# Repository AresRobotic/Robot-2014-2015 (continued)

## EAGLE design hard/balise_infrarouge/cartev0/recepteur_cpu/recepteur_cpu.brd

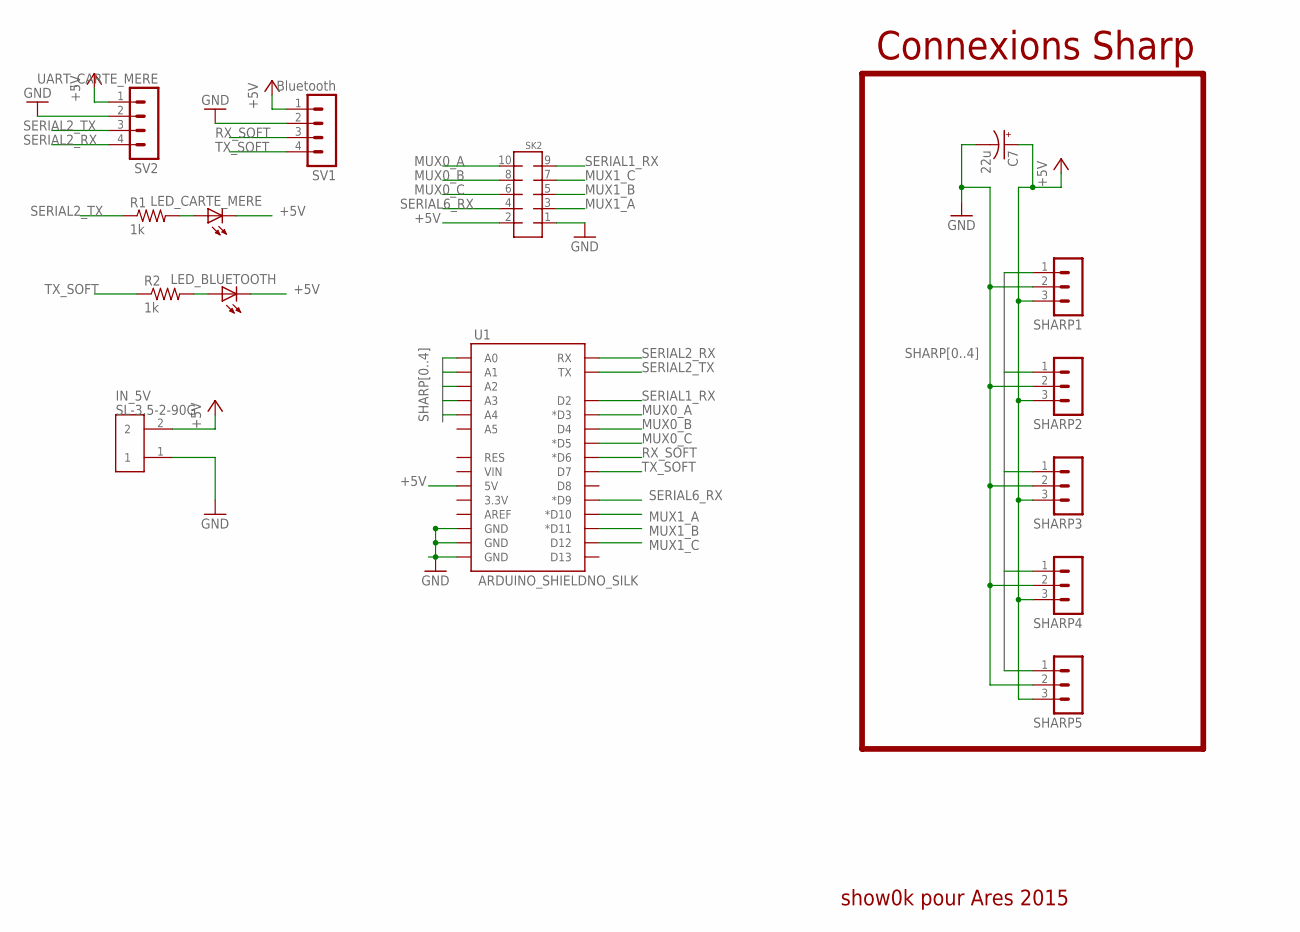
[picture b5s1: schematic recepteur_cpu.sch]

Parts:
C7: 22u; CPOL-RADIAL-100UF-25V
IN_5V: SL-3.5-2-90G
LED_BLUETOOTH: LEDCHIPLED_0805; CHIPLED_0805
LED_CARTE_MERE: LEDCHIPLED_0805; CHIPLED_0805
R1, R2: 1k; 0805
SHARP1, SHARP2, SHARP3, SHARP4, SHARP5: MA03-1
SK2: MMATCH-10-PTH; AMP-215079-10
SV1: Bluetooth; MA04-1
SV2: UART_CARTE_MERE; MA04-1
U1: ARDUINO_SHIELDNO_SILK; DUEMILANOVE_VIAS

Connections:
+5V: C7.1 (+), IN_5V.2, LED_BLUETOOTH.C, LED_CARTE_MERE.C, SHARP1.3, SHARP2.3, SHARP3.3, SHARP4.3, SHARP5.3, SK2.2, SV1.1, SV2.1, U1.5V
GND: C7.2 (-), IN_5V.1, SHARP1.2, SHARP2.2, SHARP3.2, SHARP4.2, SHARP5.2, SK2.1, SV1.2, SV2.2, U1.GND@0 (GND), U1.GND@1 (GND), U1.GND@2 (GND)
MUX0_A: SK2.10, U1.D3 (*D3)
MUX0_B: SK2.8, U1.D4
MUX0_C: SK2.6, U1.D5 (*D5)
MUX1_A: SK2.3, U1.D10 (*D10)
MUX1_B: SK2.5, U1.D11 (*D11)
MUX1_C: SK2.7, U1.D12
unnamed: LED_BLUETOOTH.A, R2.2
unnamed: LED_CARTE_MERE.A, R1.2
RX_SOFT: SV1.3, U1.D6 (*D6)
SERIAL1_RX: SK2.9, U1.D2
SERIAL2_RX: SV2.4, U1.RX
SERIAL2_TX: R1.1, SV2.3, U1.TX
SERIAL6_RX: SK2.4, U1.D9 (*D9)
SHARP0: SHARP1.1, U1.A0
SHARP1: SHARP2.1, U1.A1
SHARP2: SHARP3.1, U1.A2
SHARP3: SHARP4.1, U1.A3
SHARP4: SHARP5.1, U1.A4
TX_SOFT: R2.1, SV1.4, U1.D7

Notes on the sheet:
Connexions Sharp
show0k pour Ares 2015

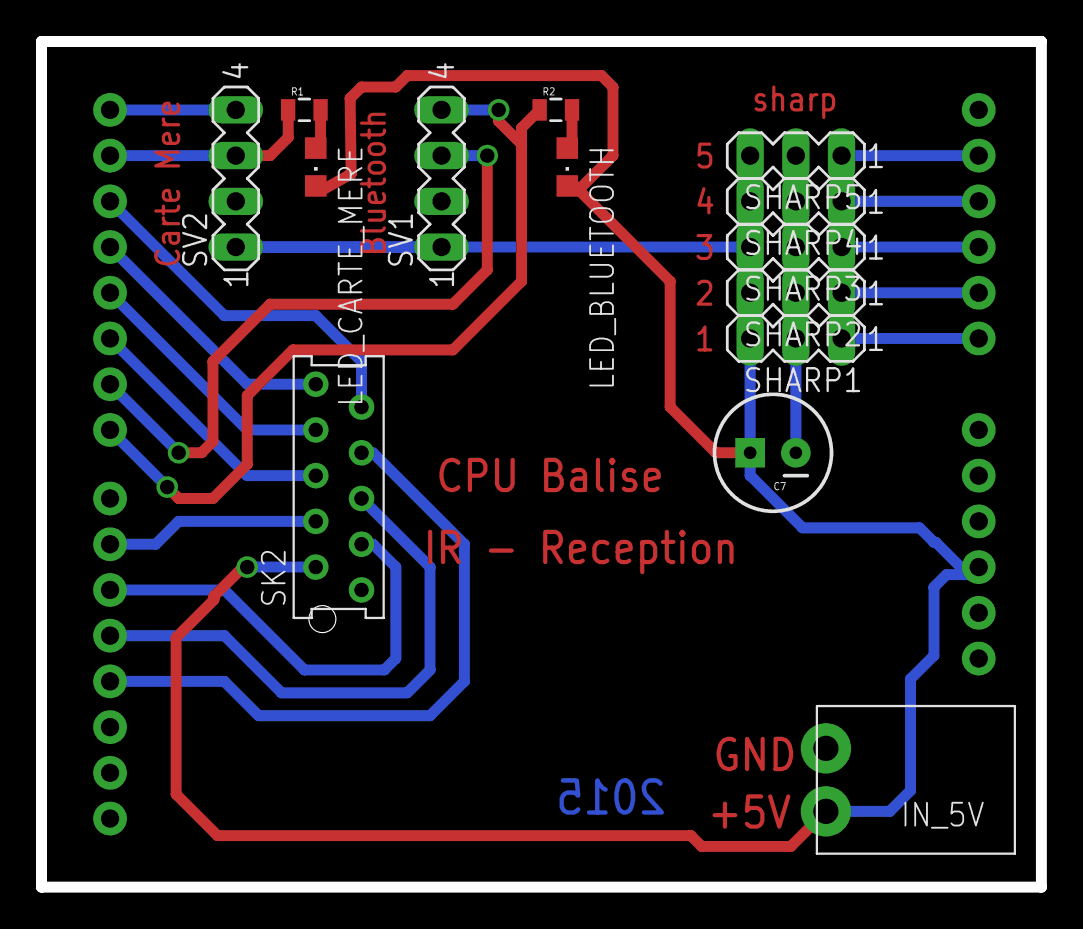
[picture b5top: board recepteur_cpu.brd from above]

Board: 2 copper layers, 55.6 x 47.0 mm, 15 parts (0 on the bottom side), 21 nets.

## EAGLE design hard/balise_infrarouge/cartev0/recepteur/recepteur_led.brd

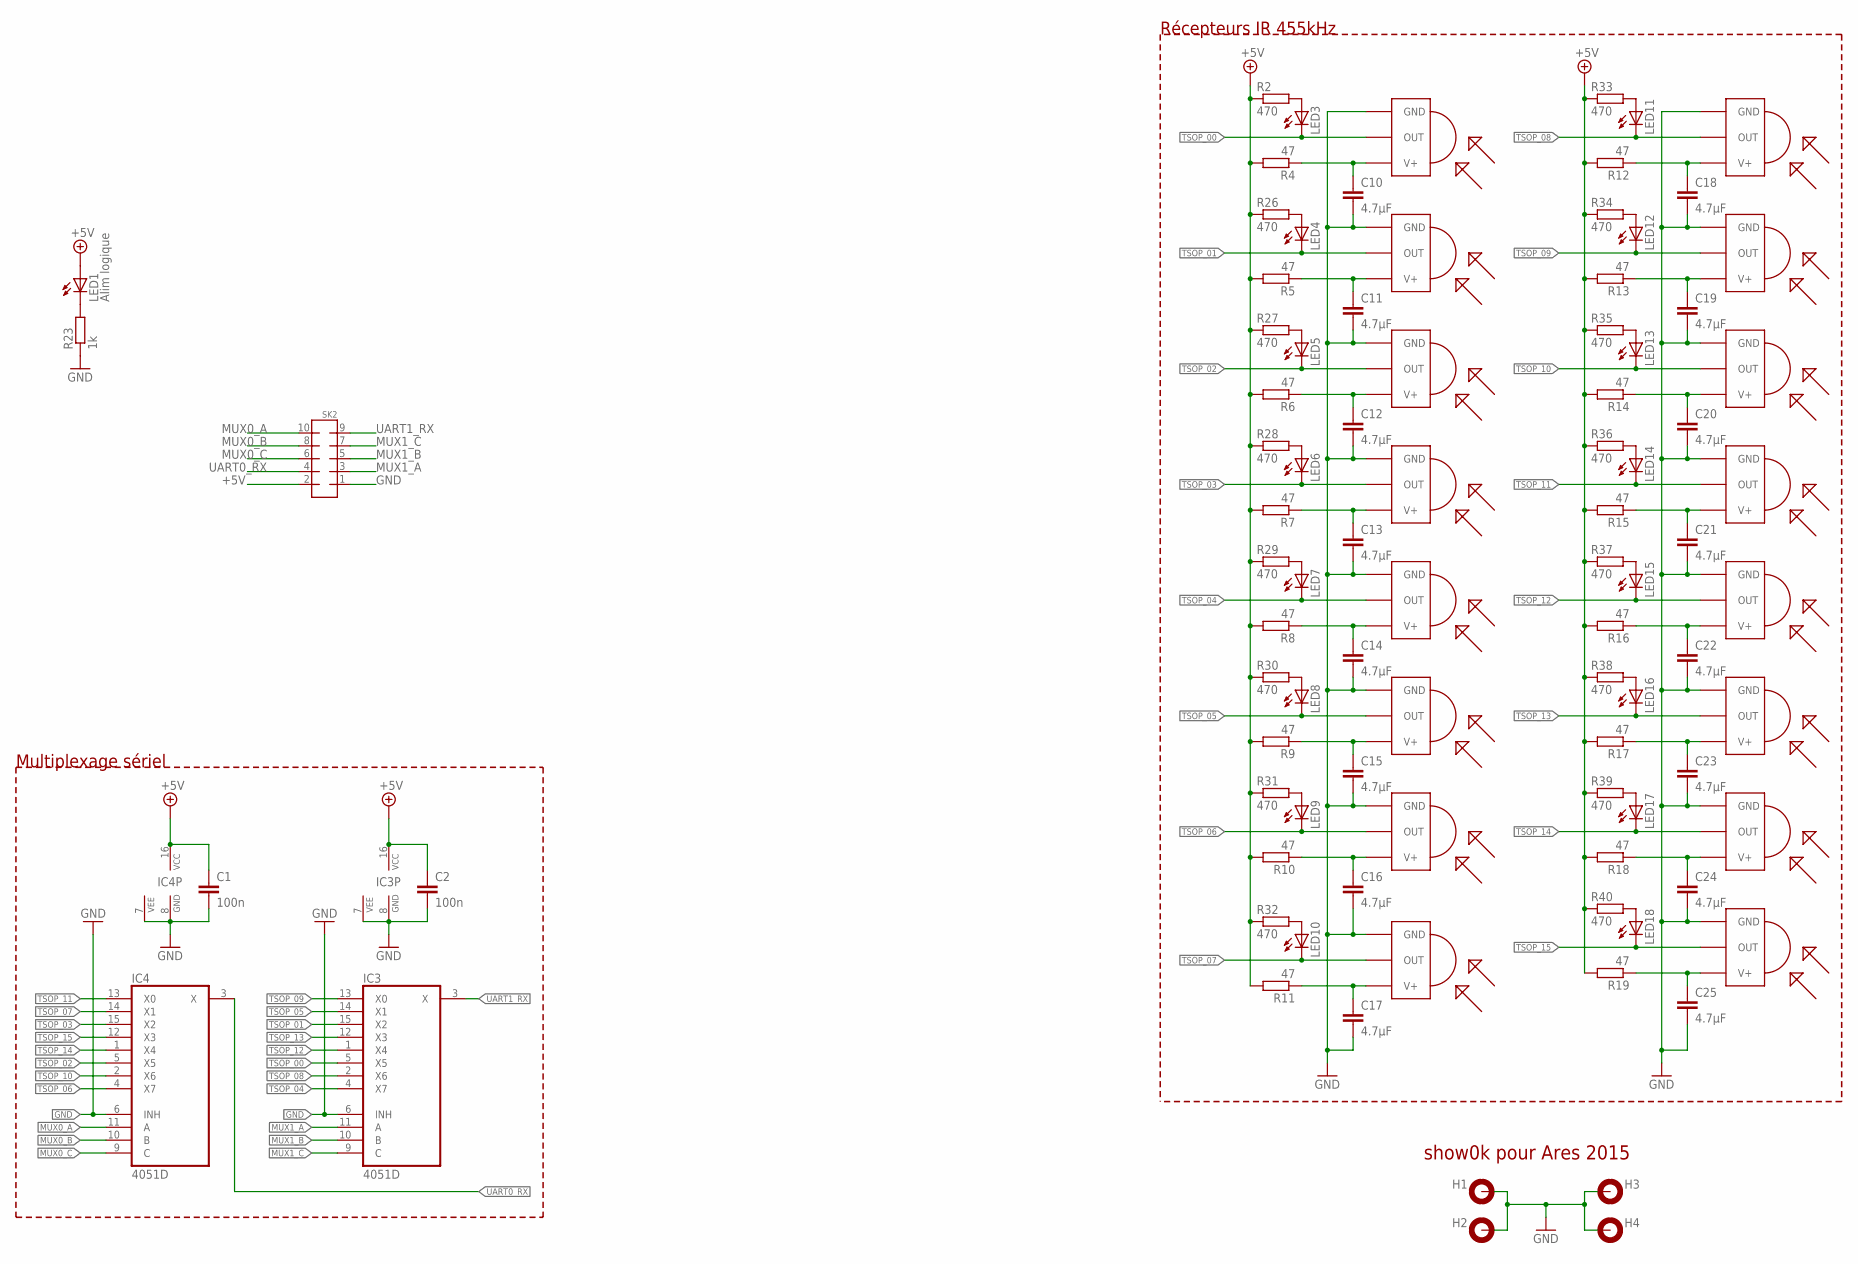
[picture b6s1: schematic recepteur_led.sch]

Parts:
C1, C2: 100n; C0805
C10, C11, C12, C13, C14, C15, C16, C17, C18, C19, C20, C21, C22, C23, C24, C25: 4.7µF; C0805
H1, H2, H3, H4: MOUNT-PAD-ROUND3.0; 3,0-PAD
IC3, IC4: 4051D; SO16
LED1: Alim logique; CHIP-LED0805
LED3, LED4, LED5, LED6, LED7, LED8, LED9, LED10, LED11, LED12, LED13, LED14, LED15, LED16, LED17, LED18: LEDCHIP-LED0805; CHIP-LED0805
R2, R26, R27, R28, R29, R30, R31, R32, R33, R34, R35, R36, R37, R38, R39, R40: 470; R0805
R4, R5, R6, R7, R8, R9, R10, R11, R12, R13, R14, R15, R16, R17, R18, R19: 47; R0805
R23: 1k; M0805
SK2: MMATCH-10-PTH; AMP-215079-10
TSOP00, TSOP01, TSOP02, TSOP03, TSOP04, TSOP05, TSOP06, TSOP07, TSOP08, TSOP09, TSOP10, TSOP11, TSOP12, TSOP13, TSOP14, TSOP15: TSOP7000; TSOP18XX

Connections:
+5V: C1.1, C2.1, IC3.16 (VCC), IC4.16 (VCC), LED1.A, R2.1, R4.2, R5.2, R6.2, R7.2, R8.2, R9.2, R10.2, R11.2, R12.2, R13.2, R14.2, R15.2, R16.2, R17.2, R18.2, R19.2, R26.1, R27.1, R28.1, R29.1, R30.1, R31.1, R32.1, R33.1, R34.1, R35.1, R36.1, R37.1, R38.1, R39.1, R40.1, SK2.2
GND: C1.2, C2.2, C10.2, C11.2, C12.2, C13.2, C14.2, C15.2, C16.2, C17.2, C18.2, C19.2, C20.2, C21.2, C22.2, C23.2, C24.2, C25.2, H1.B3,0, H2.B3,0, H3.B3,0, H4.B3,0, IC3.6 (INH), IC3.7 (VEE), IC3.8 (GND), IC4.6 (INH), IC4.7 (VEE), IC4.8 (GND), R23.1, SK2.1, TSOP00.GND, TSOP01.GND, TSOP02.GND, TSOP03.GND, TSOP04.GND, TSOP05.GND, TSOP06.GND, TSOP07.GND, TSOP08.GND, TSOP09.GND, TSOP10.GND, TSOP11.GND, TSOP12.GND, TSOP13.GND, TSOP14.GND, TSOP15.GND
MUX0_A: IC4.11 (A), SK2.10
MUX0_B: IC4.10 (B), SK2.8
MUX0_C: IC4.9 (C), SK2.6
MUX1_A: IC3.11 (A), SK2.3
MUX1_B: IC3.10 (B), SK2.5
MUX1_C: IC3.9 (C), SK2.7
unnamed: LED3.A, R2.2
unnamed: LED4.A, R26.2
unnamed: LED5.A, R27.2
unnamed: LED6.A, R28.2
unnamed: LED7.A, R29.2
unnamed: C10.1, R4.1, TSOP00.VCC (V+)
unnamed: C11.1, R5.1, TSOP01.VCC (V+)
unnamed: C12.1, R6.1, TSOP02.VCC (V+)
unnamed: C13.1, R7.1, TSOP03.VCC (V+)
unnamed: LED1.C, R23.2
unnamed: LED8.A, R30.2
unnamed: LED9.A, R31.2
unnamed: LED10.A, R32.2
unnamed: LED11.A, R33.2
unnamed: C14.1, R8.1, TSOP04.VCC (V+)
unnamed: C15.1, R9.1, TSOP05.VCC (V+)
unnamed: C16.1, R10.1, TSOP06.VCC (V+)
unnamed: LED12.A, R34.2
unnamed: LED13.A, R35.2
unnamed: LED14.A, R36.2
unnamed: LED15.A, R37.2
unnamed: LED16.A, R38.2
unnamed: LED17.A, R39.2
unnamed: LED18.A, R40.2
unnamed: C17.1, R11.1, TSOP07.VCC (V+)
unnamed: C25.1, R19.1, TSOP15.VCC (V+)
unnamed: C24.1, R18.1, TSOP14.VCC (V+)
unnamed: C23.1, R17.1, TSOP13.VCC (V+)
unnamed: C22.1, R16.1, TSOP12.VCC (V+)
unnamed: C21.1, R15.1, TSOP11.VCC (V+)
unnamed: C19.1, R13.1, TSOP09.VCC (V+)
unnamed: C20.1, R14.1, TSOP10.VCC (V+)
unnamed: C18.1, R12.1, TSOP08.VCC (V+)
TSOP_00: IC3.5 (X5), LED3.C, TSOP00.OUT
TSOP_01: IC3.15 (X2), LED4.C, TSOP01.OUT
TSOP_02: IC4.5 (X5), LED5.C, TSOP02.OUT
TSOP_03: IC4.15 (X2), LED6.C, TSOP03.OUT
TSOP_04: IC3.4 (X7), LED7.C, TSOP04.OUT
TSOP_05: IC3.14 (X1), LED8.C, TSOP05.OUT
TSOP_06: IC4.4 (X7), LED9.C, TSOP06.OUT
TSOP_07: IC4.14 (X1), LED10.C, TSOP07.OUT
TSOP_08: IC3.2 (X6), LED11.C, TSOP08.OUT
TSOP_09: IC3.13 (X0), LED12.C, TSOP09.OUT
TSOP_10: IC4.2 (X6), LED13.C, TSOP10.OUT
TSOP_11: IC4.13 (X0), LED14.C, TSOP11.OUT
TSOP_12: IC3.1 (X4), LED15.C, TSOP12.OUT
TSOP_13: IC3.12 (X3), LED16.C, TSOP13.OUT
TSOP_14: IC4.1 (X4), LED17.C, TSOP14.OUT
TSOP_15: IC4.12 (X3), LED18.C, TSOP15.OUT
UART0_RX: IC4.3 (X), SK2.4
UART1_RX: IC3.3 (X), SK2.9

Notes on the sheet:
Multiplexage sériel
Récepteurs IR 455kHz
show0k pour Ares 2015

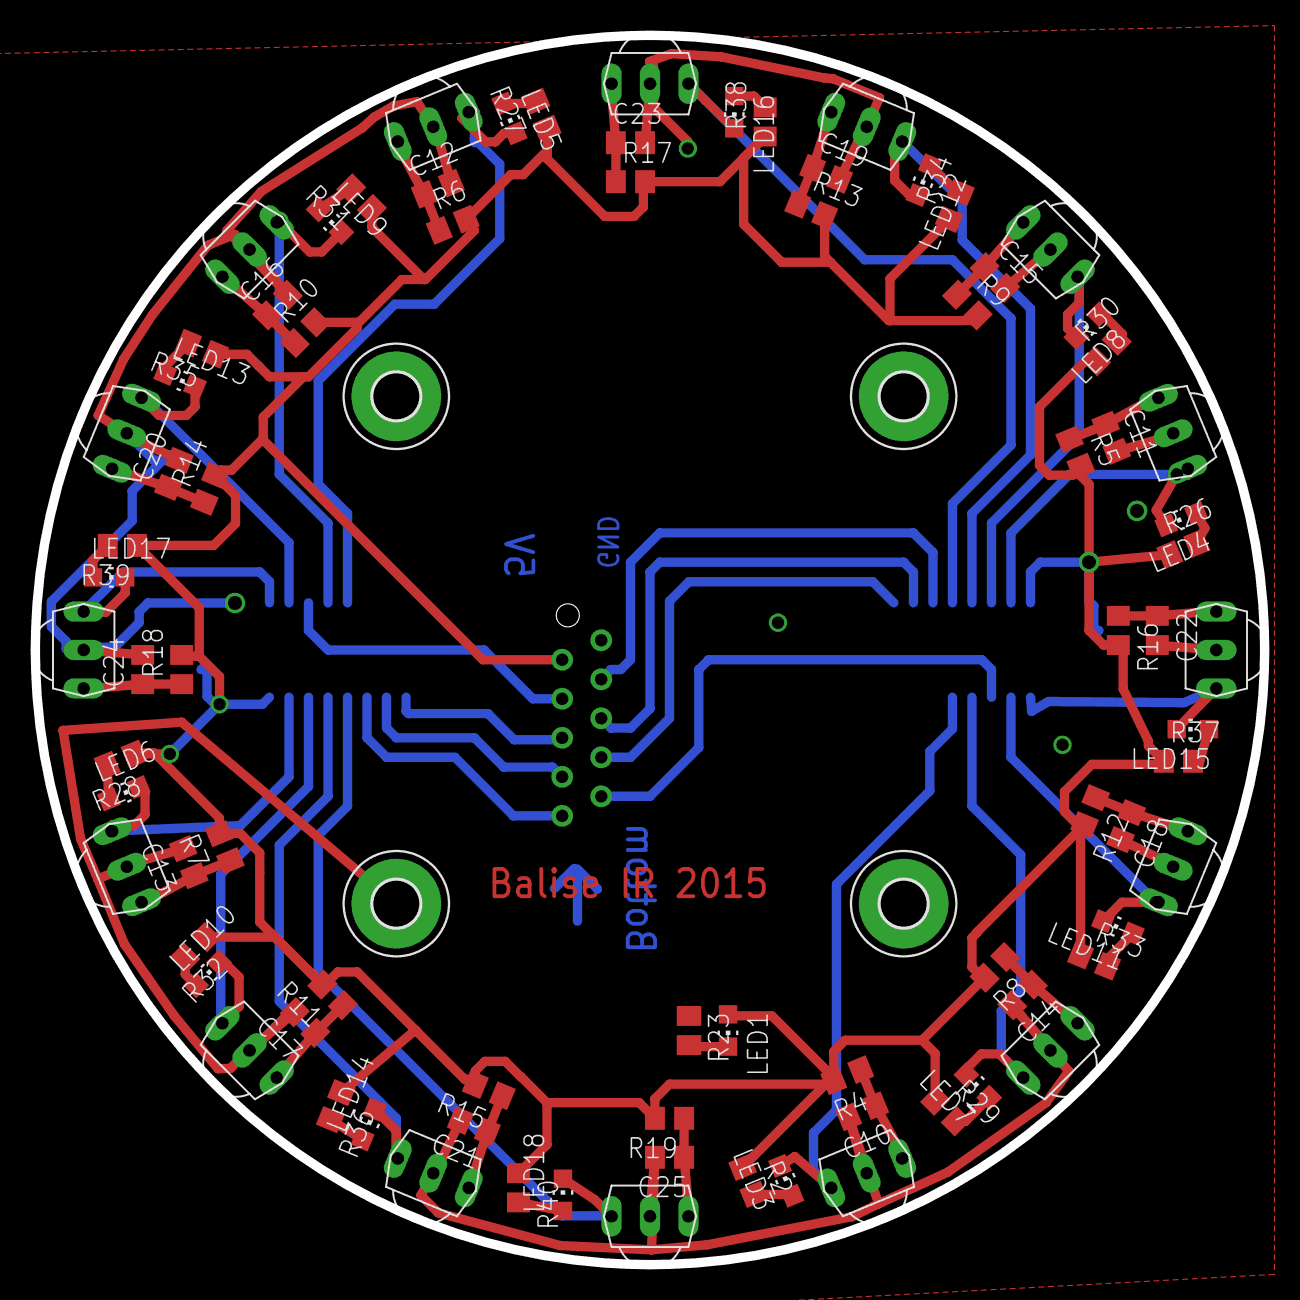
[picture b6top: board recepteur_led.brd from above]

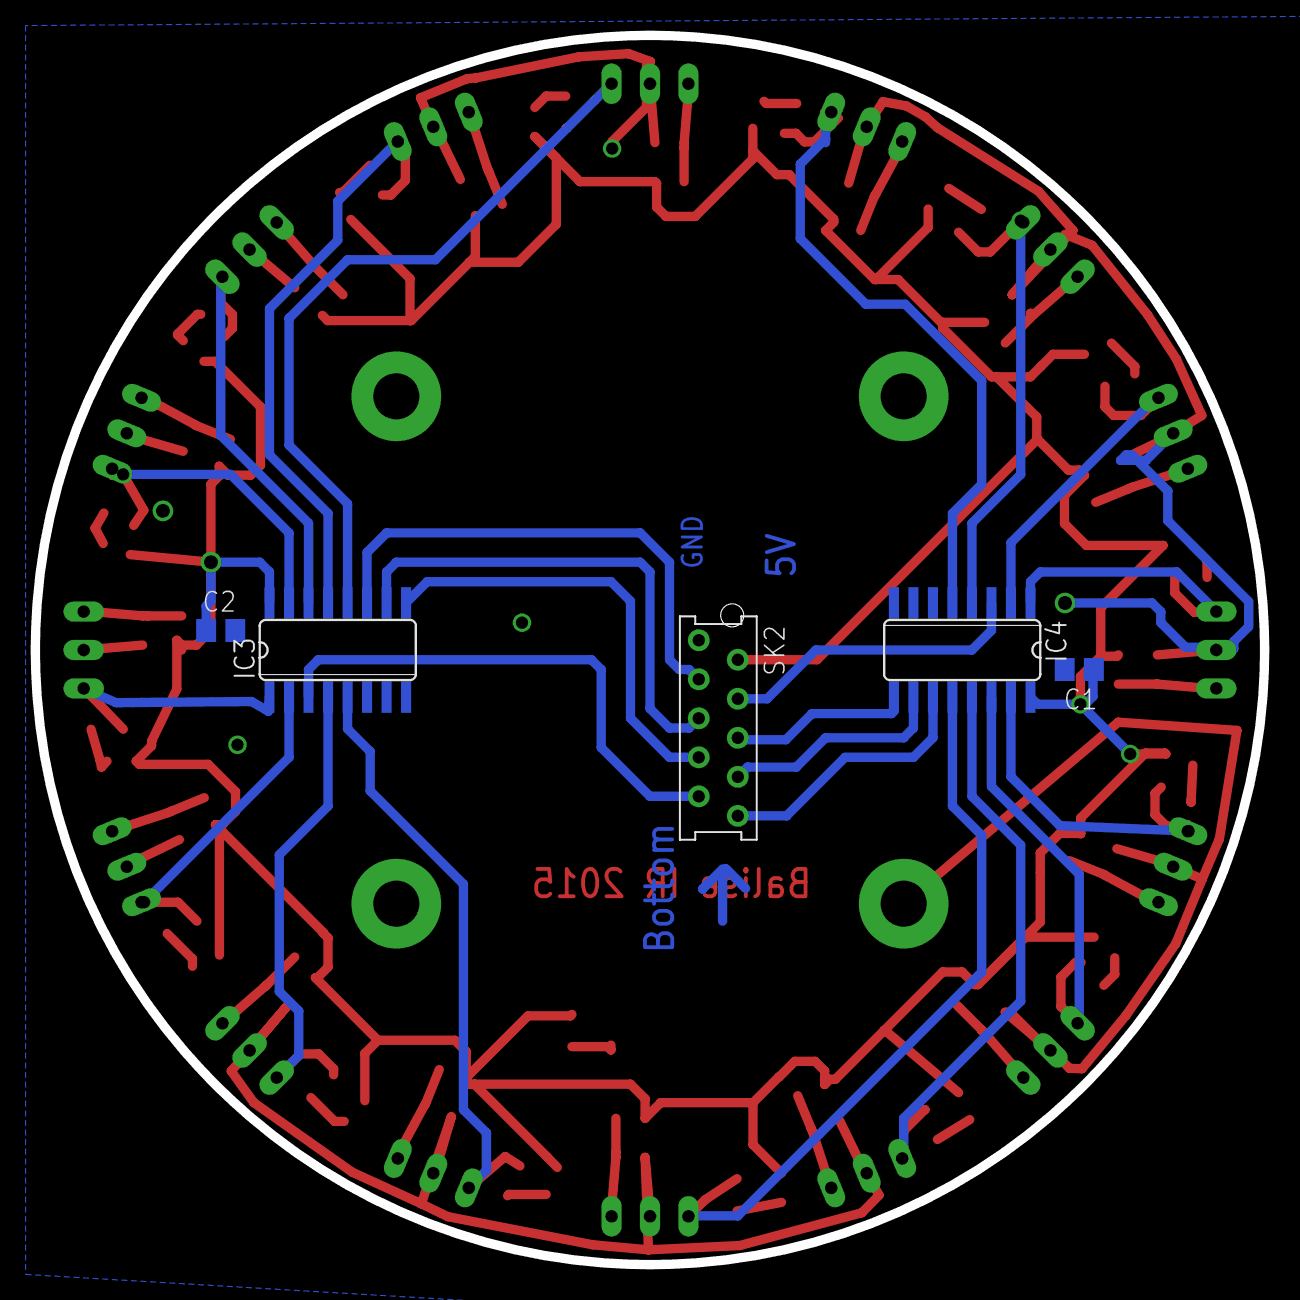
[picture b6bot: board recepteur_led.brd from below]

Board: 2 copper layers, 80.0 x 80.0 mm, 91 parts (5 on the bottom side), 59 nets.

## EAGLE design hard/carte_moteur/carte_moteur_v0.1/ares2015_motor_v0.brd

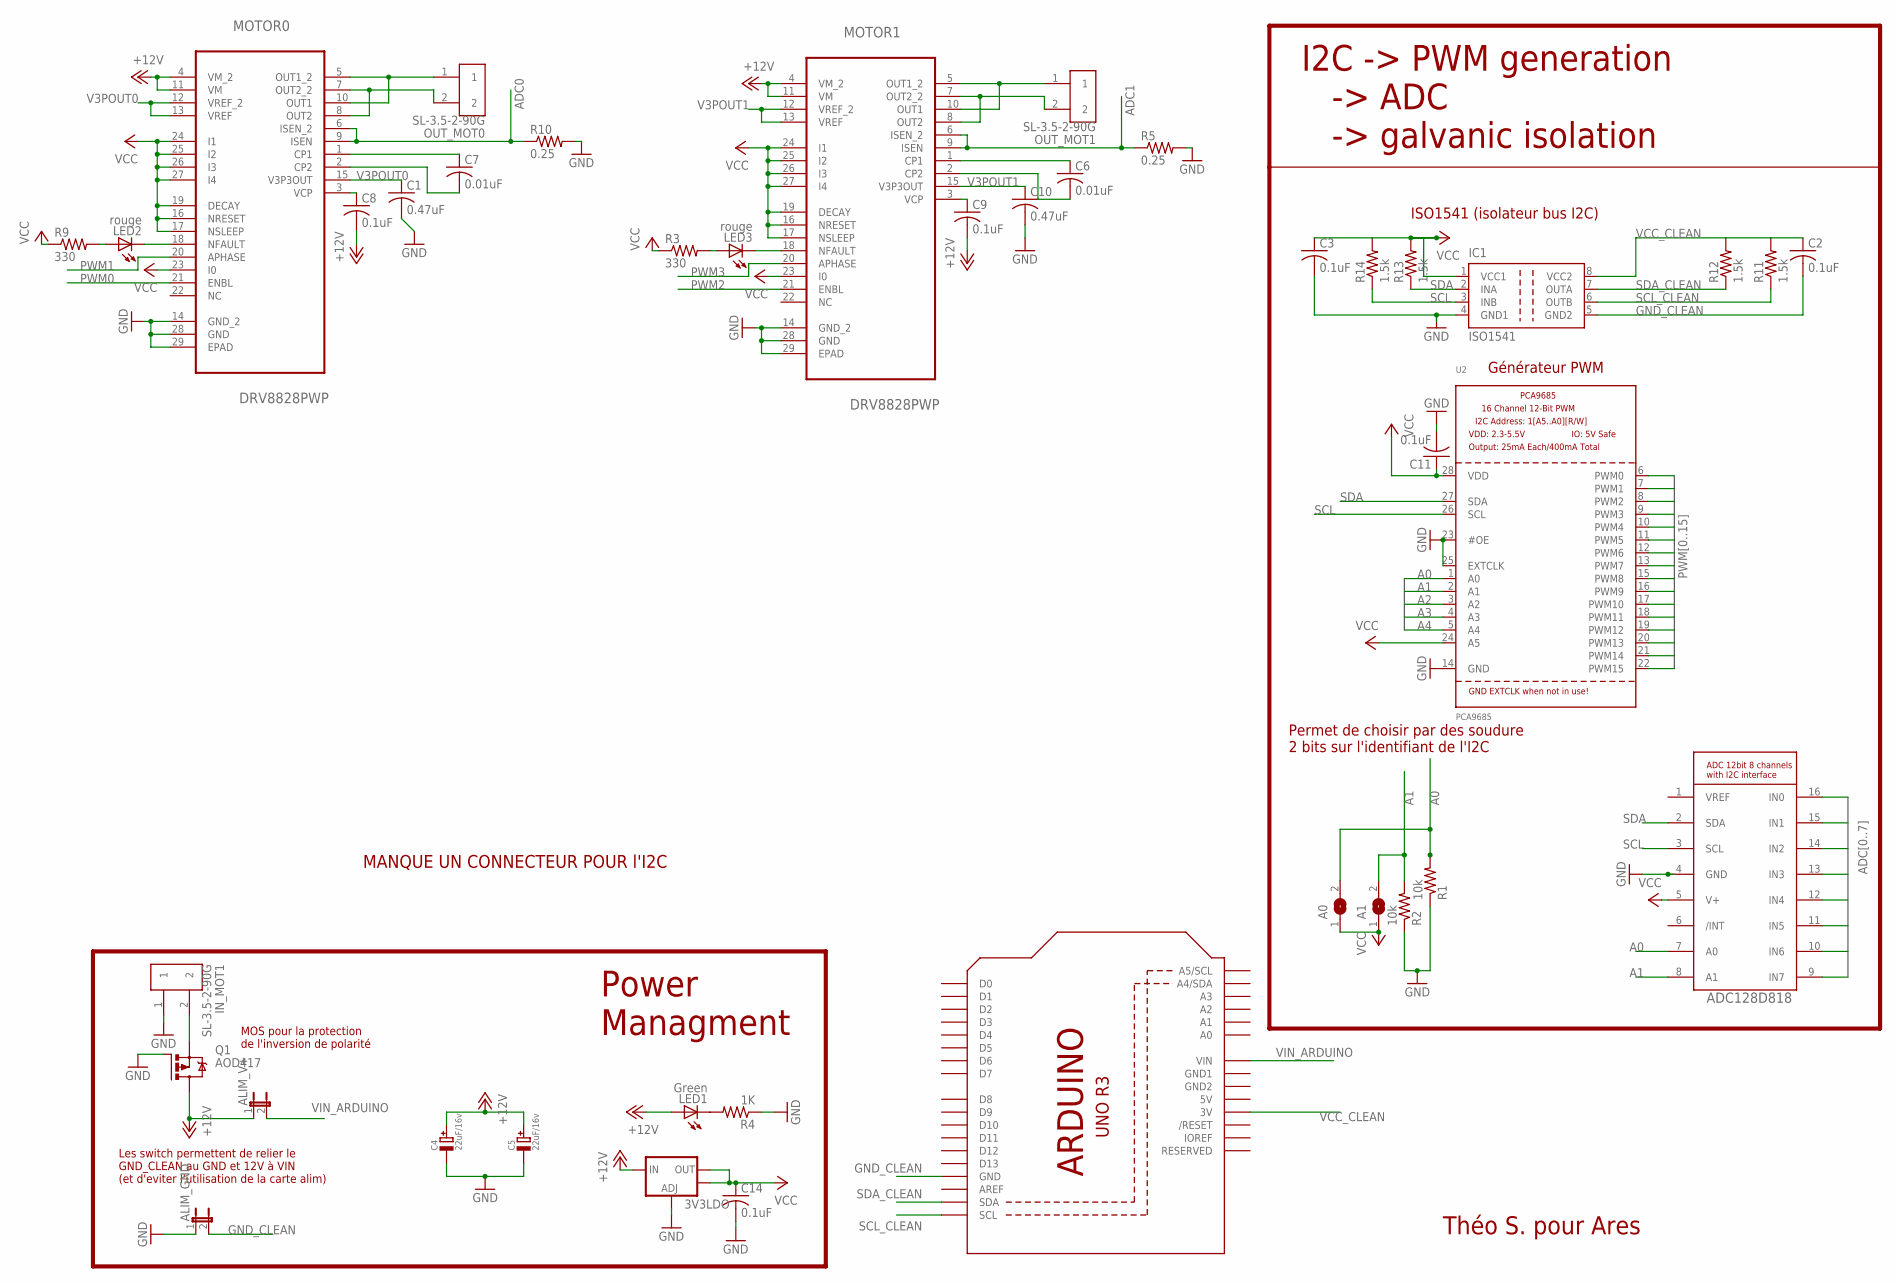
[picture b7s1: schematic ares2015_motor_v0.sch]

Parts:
3V3LDO: V_REG_LM1117SOT223; SOT223; MPN ACT108W-600D
A0, A1: SJ
ALIM_GND: JP1E; JP1
ALIM_V+: JP1E; JP1
C1, C10: 0.47uF; C0805K; MPN 04026D474KAT2A
C2, C3, C8, C9, C11, C14: 0.1uF; C0805K; MPN 02016D104KAT2A
C4, C5: 22uF/16v; PANASONIC_C
C6, C7: 0.01uF; C0805K; MPN 0201ZC103KAT2A
IC1: ISO1541; SO-08
IN_MOT1: SL-3.5-2-90G; MPN SL 3.5/2/90G
LED1: Green; CHIP-LED0805
LED2, LED3: rouge; CHIPLED_0805
MOTOR0, MOTOR1: DRV8828PWP; SOP65P640X120-29N
OUT_MOT0, OUT_MOT1: SL-3.5-2-90G; MPN SL 3.5/2/90G
Q1: AOD417; D-PAK_TO252AA
R1, R2: 10k; M0805
R3, R9: 330; M0805
R4: 1K; M0805
R5, R10: 0.25; M0805
R11, R12, R13, R14: 1.5k; M0805
U1: ARDUINOR3-BPLACE
U2: PCA9685; TSSOP28
U$6: LMD128D818; ADC128D818

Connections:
+12V: 3V3LDO.3 (IN), ALIM_V+.1, C4.+, C5.+, C8.2, C9.2, LED1.A, MOTOR0.4 (VM_2), MOTOR0.11 (VM), MOTOR1.4 (VM_2), MOTOR1.11 (VM), Q1.4 (D)
/RST: U1.RESET (/RESET)
A0: A0.2, R1.2, U2.1 (A0), U$6.7 (A0)
A1: A1.2, R2.2, U2.2 (A1), U$6.8 (A1)
A2: U2.3 (A2)
A3: U2.4 (A3)
A4: U2.5 (A4)
ADC0: MOTOR0.6 (ISEN_2), MOTOR0.9 (ISEN), R10.1, U$6.16 (IN0)
ADC1: MOTOR1.6 (ISEN_2), MOTOR1.9 (ISEN), R5.1, U$6.15 (IN1)
ADC2: U$6.14 (IN2)
ADC3: U$6.13 (IN3)
ADC4: U$6.12 (IN4)
ADC5: U$6.11 (IN5)
ADC6: U$6.10 (IN6)
ADC7: U$6.9 (IN7)
GND: 3V3LDO.1 (ADJ), ALIM_GND.1, C1.2, C3.2, C4.-, C5.-, C10.2, C11.2, C14.2, IC1.4 (GND1), IN_MOT1.1, MOTOR0.14 (GND_2), MOTOR0.28 (GND), MOTOR0.29 (EPAD), MOTOR1.14 (GND_2), MOTOR1.28 (GND), MOTOR1.29 (EPAD), Q1.1 (G), R1.1, R2.1, R4.1, R5.2, R10.2, U2.14 (GND), U2.23 (#OE), U2.25 (EXTCLK), U$6.4 (GND)
GND1: U1.GND1
GND2: U1.GND2
GND_CLEAN: ALIM_GND.2, C2.2, IC1.5 (GND2), U1.GND
unnamed: C6.1, MOTOR1.1 (CP1)
unnamed: MOTOR0.7 (OUT2_2), MOTOR0.8 (OUT2), OUT_MOT0.2
unnamed: C6.2, MOTOR1.2 (CP2)
unnamed: C9.1, MOTOR1.3 (VCP)
unnamed: MOTOR0.5 (OUT1_2), MOTOR0.10 (OUT1), OUT_MOT0.1
unnamed: LED3.C, MOTOR1.18 (NFAULT)
unnamed: LED3.A, R3.2
unnamed: MOTOR1.5 (OUT1_2), MOTOR1.10 (OUT1), OUT_MOT1.1
unnamed: MOTOR1.7 (OUT2_2), MOTOR1.8 (OUT2), OUT_MOT1.2
unnamed: C7.1, MOTOR0.1 (CP1)
unnamed: C7.2, MOTOR0.2 (CP2)
unnamed: C8.1, MOTOR0.3 (VCP)
unnamed: LED2.A, R9.2
unnamed: LED2.C, MOTOR0.18 (NFAULT)
unnamed: LED1.C, R4.2
unnamed: IN_MOT1.2, Q1.3 (S)
PWM0: MOTOR0.21 (ENBL), U2.6 (PWM0)
PWM0A: U1.D6
PWM0B: U1.D5
PWM1: MOTOR0.20 (APHASE), U2.7 (PWM1)
PWM1B: U1.D10
PWM2: MOTOR1.21 (ENBL), U2.8 (PWM2)
PWM2A: U1.D11
PWM2B: U1.D3
PWM3: MOTOR1.20 (APHASE), U2.9 (PWM3)
PWM4: U2.10 (PWM4)
PWM5: U2.11 (PWM5)
PWM6: U2.12 (PWM6)
PWM7: U2.13 (PWM7)
PWM8: U2.15 (PWM8)
PWM9: U2.16 (PWM9)
PWM10: U2.17 (PWM10)
PWM11: U2.18 (PWM11)
PWM12: U2.19 (PWM12)
PWM13: U2.20 (PWM13)
PWM14: U2.21 (PWM14)
PWM15: U2.22 (PWM15)
SCL: IC1.3 (INB), R14.1, U2.26 (SCL), U$6.3 (SCL)
SCL_CLEAN: IC1.6 (OUTB), R11.1, U1.SCL
SDA: IC1.2 (INA), R13.1, U2.27 (SDA), U$6.2 (SDA)
SDA_CLEAN: IC1.7 (OUTA), R12.1, U1.SDA
V3POUT0: C1.1, MOTOR0.12 (VREF_2), MOTOR0.13 (VREF), MOTOR0.15 (V3P3OUT)
V3POUT1: C10.1, MOTOR1.12 (VREF_2), MOTOR1.13 (VREF), MOTOR1.15 (V3P3OUT)
VCC: 3V3LDO.2 (OUT), 3V3LDO.4 (OUT), A0.1, A1.1, C3.1, C11.1, C14.1, IC1.1 (VCC1), MOTOR0.16 (NRESET), MOTOR0.17 (NSLEEP), MOTOR0.19 (DECAY), MOTOR0.23 (I0), MOTOR0.24 (I1), MOTOR0.25 (I2), MOTOR0.26 (I3), MOTOR0.27 (I4), MOTOR1.16 (NRESET), MOTOR1.17 (NSLEEP), MOTOR1.19 (DECAY), MOTOR1.23 (I0), MOTOR1.24 (I1), MOTOR1.25 (I2), MOTOR1.26 (I3), MOTOR1.27 (I4), R3.1, R9.1, R13.2, R14.2, U2.24 (A5), U2.28 (VDD), U$6.5 (V+)
VCC_CLEAN: C2.1, IC1.8 (VCC2), R11.2, R12.2, U1.3V
VIN_ARDUINO: ALIM_V+.2, U1.VIN

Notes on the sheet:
ISO1541 (isolateur bus I2C)
Générateur PWM
Permet de choisir par des soudure 2 bits sur l'identifiant de l'I2C
Les switch permettent de relier le GND_CLEAN au GND et 12V à VIN (et d'eviter l'utilisation de la carte alim)
I2C -> PWM generation -> ADC -> galvanic isolation
Power Managment
Théo S. pour Ares
MANQUE UN CONNECTEUR POUR l'I2C
MOS pour la protection de l'inversion de polarité

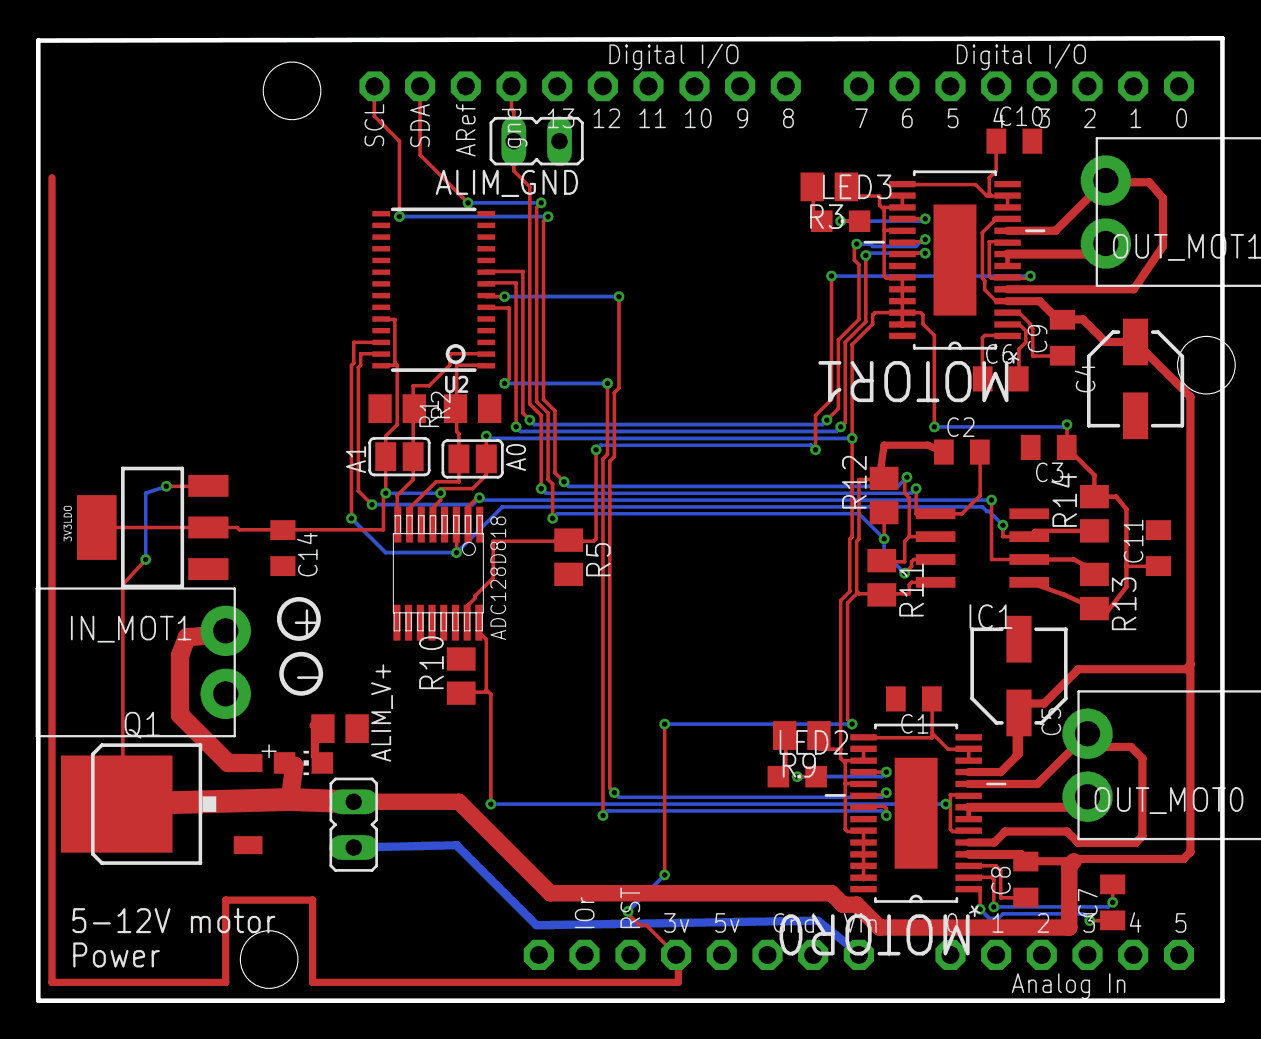
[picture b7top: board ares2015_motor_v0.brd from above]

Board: 2 copper layers, 65.8 x 53.5 mm, 41 parts (0 on the bottom side), 36 nets.

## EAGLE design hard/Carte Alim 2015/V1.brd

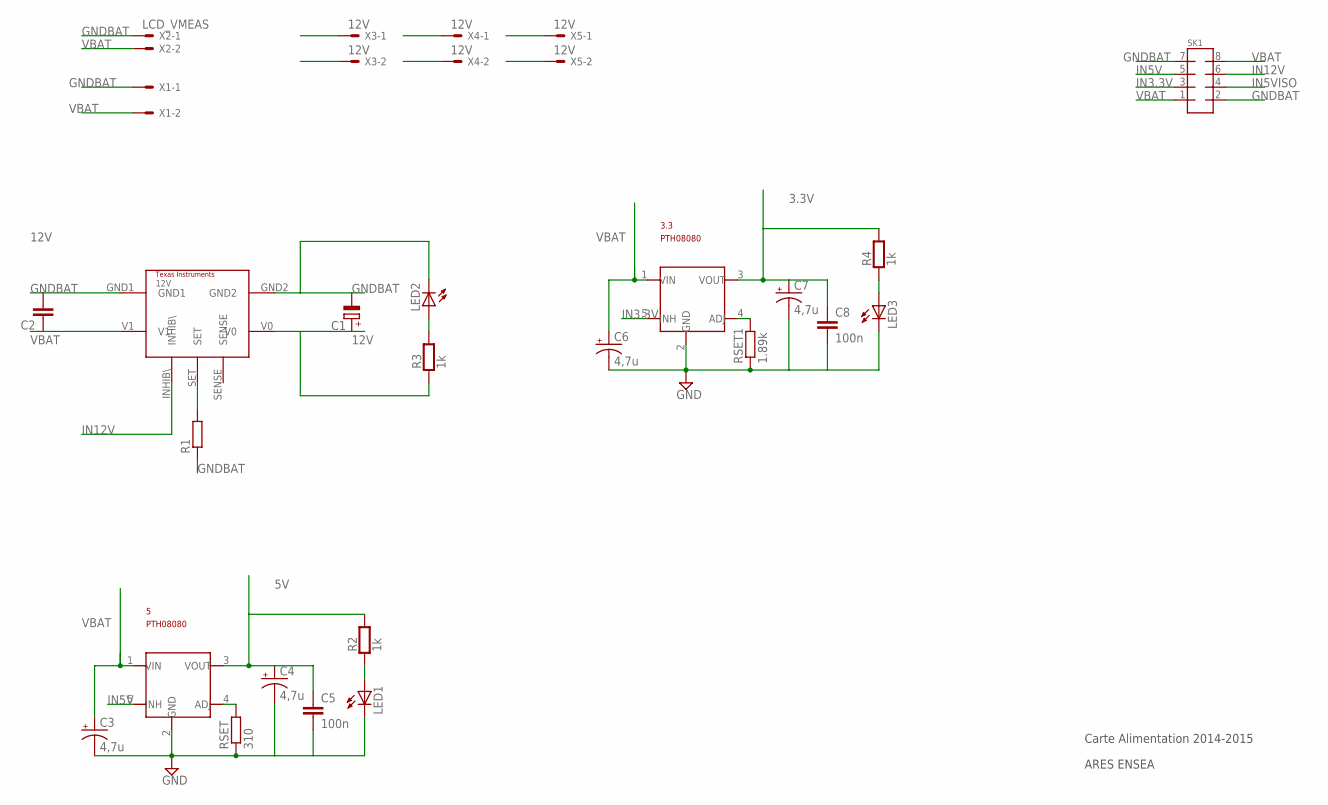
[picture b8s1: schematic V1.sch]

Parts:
3.3, 5: PTH08080; PTH08080EUF
12V: PTN78060W
C1: CPOL-EUE2-4; E2-4
C2: C-EU025-024X044; C025-024X044
C3, C4, C6, C7: 4,7u; CPOL-RADIAL-10UF-25V
C5, C8: 100n; CAP-PTH-SMALL2
LED1, LED2, LED3: LEDSML0805; SML0805
R1: R-EU_M0805; M0805
R2, R3, R4: 1k; 0805
RSET: 310; R0805
RSET1: 1.89k; R0805
SK1: MMATCH-8-PTH; AMP-215079-8
X1: KK-156-2
X2: LCD_VMEAS; 22-23-2021
X3, X4, X5: 12V; KK-156-2

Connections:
3.3V: 3.3.3 (VOUT), C7.1 (+), C8.1, R4.2
5V: 5.3 (VOUT), C4.1 (+), C5.1, R2.2
12V: 12V.V0, C1.+, R3.1, X3.1
12V1: X4.1
12V2: X5.1
GNDBAT: 3.3.2 (GND), 5.2 (GND), 12V.GND1, 12V.GND2, C1.-, C2.2, C3.2 (-), C4.2 (-), C5.2, C6.2 (-), C7.2 (-), C8.2, LED1.C, LED2.C, LED3.C, R1.1, RSET.1, RSET1.1, SK1.2, SK1.7, X1.1, X2.1, X3.2
GNDBAT1: X4.2
GNDBAT2: X5.2
IN3.3V: 3.3.5 (INH), SK1.3
IN5V: 5.5 (INH), SK1.5
IN5VISO: SK1.4
IN12V: 12V.INHIB\, SK1.6
unnamed: LED1.A, R2.1
unnamed: LED2.A, R3.2
unnamed: 3.3.4 (ADJ), RSET1.2
unnamed: 5.4 (ADJ), RSET.2
unnamed: 12V.SET, R1.2
unnamed: LED3.A, R4.1
VBAT: 3.3.1 (VIN), 5.1 (VIN), 12V.V1, C2.1, C3.1 (+), C6.1 (+), SK1.1, SK1.8, X1.2, X2.2

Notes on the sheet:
12V
Carte Alimentation 2014-2015
ARES ENSEA

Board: 2 copper layers, 26 parts (3 on the bottom side), 14 nets, no tracks yet.

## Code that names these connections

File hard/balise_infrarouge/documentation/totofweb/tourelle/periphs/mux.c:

/*
 * Carte de réception de balise
 *
 * Christophe Le Lann <contact@totofweb.net>
 * http://www.totofweb.net/robots-projet-67.html
 */

//-----------------------------
// Librairies
//-----------------------------

#include <avr/io.h>				// Mapping des registres   - http://www.nongnu.org/avr-libc/user-manual/group__avr__io.html
#include <compat/deprecated.h>	// Macros sbi et cbi       - http://www.nongnu.org/avr-libc/user-manual/group__deprecated__items.html

//-----------------------------
// Librairies persos
//-----------------------------

#include "mux.h"

//-----------------------------
// Fonctions
//-----------------------------

void mux_init(void) {
	// Par défaut, les entrées INH sont en haute impédance
	cbi(MUX0_INH_DDR, MUX0_INH_PIN);
	cbi(MUX1_INH_DDR, MUX1_INH_PIN);
	cbi(MUX0_INH_PORT, MUX0_INH_PIN);
	cbi(MUX1_INH_PORT, MUX1_INH_PIN);

	sbi(MUX0_A_DDR, MUX0_A_PIN);
	sbi(MUX1_A_DDR, MUX1_A_PIN);
	sbi(MUX0_B_DDR, MUX0_B_PIN);
	sbi(MUX1_B_DDR, MUX1_B_PIN);
	sbi(MUX0_C_DDR, MUX0_C_PIN);
	sbi(MUX1_C_DDR, MUX1_C_PIN);
}

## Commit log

2014-11-06 ajout carte mere et IR
2014-11-06 ajout doc et spec
2014-11-13 ajout carte moteur
2014-11-13 Ajout lib nucleo
    Ajout de la lib Nucléo pour Eagle. V0.1, à debugger, uniquement le
    connecteur Morpho.
    A faire, ajout du connecteur Arduino
2014-11-14 début carte moteur
2014-11-14 Modif lib Nucleo
    Modif du schéma de la version Morpho
    Ajout de la version Arduino
2014-11-14 Début carte mère
    Début du schématic de la carte mère
2014-11-15 ajout doc
2014-11-16 maj schema carte moteur (80% de schema finit)
2014-11-18 maj gitignore
2014-11-19 schematic de la carte moteur finit !
2014-11-19 modifs mineures
2014-11-24 ajout carte alim
2014-11-24 routage : automatique=98,8% réussite. Reste à ajouter les deux autres hacheurs
2014-11-26 Avancé de la carte mere
2015-02-04 Meca du robot
    Partie mécanique du robot.
    Fichier SW 2014, tout est compris dedans.
2015-03-13 ajout emetteur
2015-03-14 carte emmeteur finale ?
2015-03-14 maj doc
2015-03-14 maj doc 2
2015-03-14 test
2015-03-14 Création de la carte de prototypage
2015-03-14 maj emetteur + fini recepteur part 1
2015-03-15 maj routage
2015-03-15 ajout carte d'extension nucleo
2015-03-15 maj carte extension nucleo
2015-03-16 maj connectyeur bt + ftdi carte elettrice
2015-03-19 maj doc (décompression fichiers zip
2015-03-26 Avancement de a carte v2 e proto
2015-03-29 Carte proto V2
    Fin des modification et du routage. Prête à être imprimée
2015-03-30 Ajout de la carte boutons
2015-03-31 maj boutons
